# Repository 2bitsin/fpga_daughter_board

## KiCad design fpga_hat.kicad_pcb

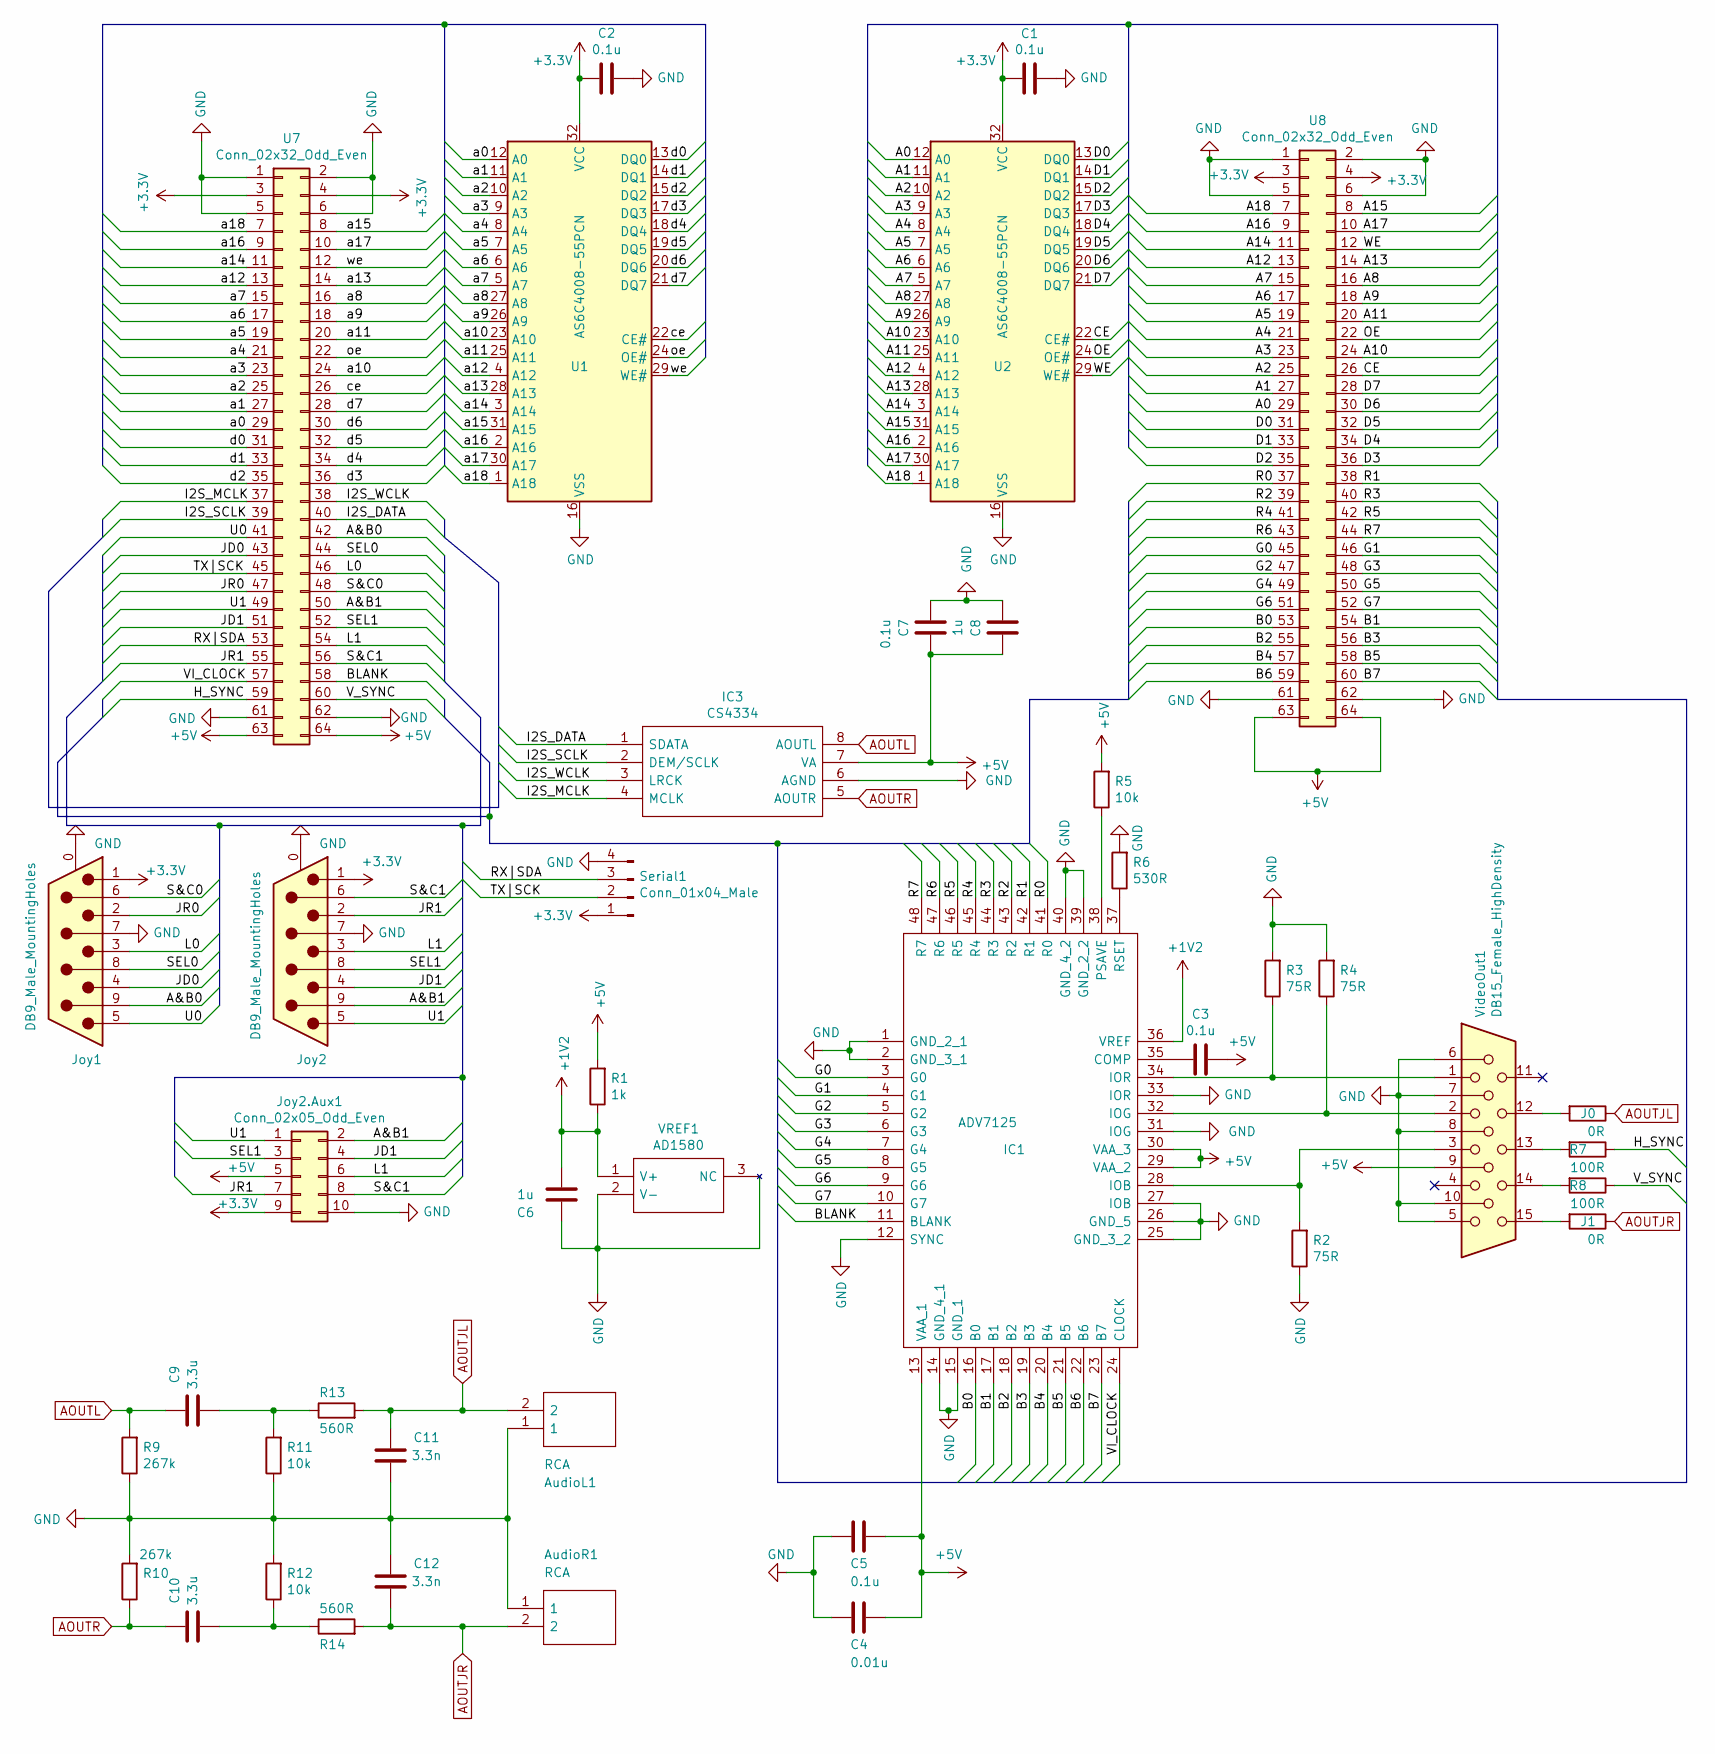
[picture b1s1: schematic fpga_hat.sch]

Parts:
AudioL1: RCA; KLPX0848A2RG
AudioR1: RCA; KLPX0848A2RG
C1, C2, C3, C5, C7: 0.1u; C_1206_3216Metric_Pad1.33x1.80mm_HandSolder
C4: 0.01u; C_1206_3216Metric_Pad1.33x1.80mm_HandSolder
C6, C8: 1u; C_1206_3216Metric_Pad1.33x1.80mm_HandSolder
C9, C10: 3.3u; C_1206_3216Metric_Pad1.33x1.80mm_HandSolder
C11, C12: 3.3n; C_1206_3216Metric_Pad1.33x1.80mm_HandSolder
IC1: ADV7125; QFP50P900X900X160-48N; Manufacturer_Part_Number ADV7125KSTZ50; Mouser Part Number 584-ADV7125KSTZ50
IC3: CS4334; SOIC127P600X175-8N; Mouser Part Number 777-CS4334-KSZ
J0, J1: 0R; R_0603_1608Metric
Joy1, Joy2: DB9_Male_MountingHoles; DSUB-9_Female_Horizontal_P2.77x2.84mm_EdgePinOffset4.94mm_H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
Joy2.Aux1: Conn_02x05_Odd_Even; PinHeader_2x05_P2.54mm_Vertical
R1: 1k; R_1206_3216Metric_Pad1.30x1.75mm_HandSolder
R2, R3, R4: 75R; R_1206_3216Metric_Pad1.30x1.75mm_HandSolder
R5, R11, R12: 10k; R_1206_3216Metric_Pad1.30x1.75mm_HandSolder
R6: 530R; R_1206_3216Metric_Pad1.30x1.75mm_HandSolder
R7, R8: 100R; R_1206_3216Metric_Pad1.30x1.75mm_HandSolder
R9, R10: 267k; R_1206_3216Metric_Pad1.30x1.75mm_HandSolder
R13, R14: 560R; R_1206_3216Metric_Pad1.30x1.75mm_HandSolder
Serial1: Conn_01x04_Male; PinHeader_1x04_P2.54mm_Vertical
U1, U2: AS6C4008-55PCN; DIP-32_W15.24mm
U7, U8: Conn_02x32_Odd_Even; PinHeader_2x32_P2.54mm_Vertical
VREF1: AD1580; SOT95P237X112-3N; Manufacturer_Part_Number AD1580BRTZ-REEL7; Mouser Part Number 584-AD1580BRTZ-R7
VideoOut1: DB15_Female_HighDensity; DSUB-15-HD_Female_Horizontal_P2.29x1.98mm_EdgePinOffset8.35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

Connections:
+1V2: C6.2, IC1.36 (VREF), R1.1, VREF1.1 (V+)
+3V3: C1.2, C2.2, Joy1.1, Joy2.1, Joy2.Aux1.9, Serial1.1, U1.32 (VCC), U2.32 (VCC), U7.3, U7.4, U8.3, U8.4
+5V: C3.1, C4.1, C5.1, C7.1, C8.1, IC1.13 (VAA_1), IC1.29 (VAA_2), IC1.30 (VAA_3), IC3.7 (VA), Joy2.Aux1.5, R1.2, R5.2, U7.63, U7.64, U8.63, U8.64, VideoOut1.9
/A0: U2.12 (A0), U8.29
/A1: U2.11 (A1), U8.27
/A2: U2.10 (A2), U8.25
/A3: U2.9 (A3), U8.23
/A4: U2.8 (A4), U8.21
/A5: U2.7 (A5), U8.19
/A6: U2.6 (A6), U8.17
/A7: U2.5 (A7), U8.15
/A8: U2.27 (A8), U8.16
/A9: U2.26 (A9), U8.18
/A10: U2.23 (A10), U8.24
/A11: U2.25 (A11), U8.20
/A12: U2.4 (A12), U8.13
/A13: U2.28 (A13), U8.14
/A14: U2.3 (A14), U8.11
/A15: U2.31 (A15), U8.8
/A16: U2.2 (A16), U8.9
/A17: U2.30 (A17), U8.10
/A18: U2.1 (A18), U8.7
/A&B0: Joy1.9, U7.42
/A&B1: Joy2.9, Joy2.Aux1.2, U7.50
/B0: IC1.16 (B0), U8.53
/B1: IC1.17 (B1), U8.54
/B2: IC1.18 (B2), U8.55
/B3: IC1.19 (B3), U8.56
/B4: IC1.20 (B4), U8.57
/B5: IC1.21 (B5), U8.58
/B6: IC1.22 (B6), U8.59
/B7: IC1.23 (B7), U8.60
/BLANK: IC1.11 (BLANK~), U7.58
/CE: U2.22 (CE#), U8.26
/D0: U2.13 (DQ0), U8.31
/D1: U2.14 (DQ1), U8.33
/D2: U2.15 (DQ2), U8.35
/D3: U2.17 (DQ3), U8.36
/D4: U2.18 (DQ4), U8.34
/D5: U2.19 (DQ5), U8.32
/D6: U2.20 (DQ6), U8.30
/D7: U2.21 (DQ7), U8.28
/G0: IC1.3 (G0), U8.45
/G1: IC1.4 (G1), U8.46
/G2: IC1.5 (G2), U8.47
/G3: IC1.6 (G3), U8.48
/G4: IC1.7 (G4), U8.49
/G5: IC1.8 (G5), U8.50
/G6: IC1.9 (G6), U8.51
/G7: IC1.10 (G7), U8.52
/H_SYNC: R7.1, U7.59
/I2S_DATA: IC3.1 (SDATA), U7.40
/I2S_MCLK: IC3.4 (MCLK), U7.37
/I2S_SCLK: IC3.2 (DEM/SCLK), U7.39
/I2S_WCLK: IC3.3 (LRCK), U7.38
/JD0: Joy1.4, U7.43
/JD1: Joy2.4, Joy2.Aux1.4, U7.51
/JR0: Joy1.2, U7.47
/JR1: Joy2.2, Joy2.Aux1.7, U7.55
/L0: Joy1.3, U7.46
/L1: Joy2.3, Joy2.Aux1.6, U7.54
/OE: U2.24 (OE#), U8.22
/R0: IC1.41 (R0), U8.37
/R1: IC1.42 (R1), U8.38
/R2: IC1.43 (R2), U8.39
/R3: IC1.44 (R3), U8.40
/R4: IC1.45 (R4), U8.41
/R5: IC1.46 (R5), U8.42
/R6: IC1.47 (R6), U8.43
/R7: IC1.48 (R7), U8.44
/RX|SDA: Serial1.3, U7.53
/S&C0: Joy1.6, U7.48
/S&C1: Joy2.6, Joy2.Aux1.8, U7.56
/SEL0: Joy1.8, U7.44
/SEL1: Joy2.8, Joy2.Aux1.3, U7.52
/TX|SCK: Serial1.2, U7.45
/U0: Joy1.5, U7.41
/U1: Joy2.5, Joy2.Aux1.1, U7.49
/VI_CLOCK: IC1.24 (CLOCK), U7.57
/V_SYNC: R8.1, U7.60
/WE: U2.29 (WE#), U8.12
/a0: U1.12 (A0), U7.29
/a1: U1.11 (A1), U7.27
/a2: U1.10 (A2), U7.25
/a3: U1.9 (A3), U7.23
/a4: U1.8 (A4), U7.21
/a5: U1.7 (A5), U7.19
/a6: U1.6 (A6), U7.17
/a7: U1.5 (A7), U7.15
/a8: U1.27 (A8), U7.16
/a9: U1.26 (A9), U7.18
/a10: U1.23 (A10), U7.24
/a11: U1.25 (A11), U7.20
/a12: U1.4 (A12), U7.13
/a13: U1.28 (A13), U7.14
/a14: U1.3 (A14), U7.11
/a15: U1.31 (A15), U7.8
/a16: U1.2 (A16), U7.9
/a17: U1.30 (A17), U7.10
/a18: U1.1 (A18), U7.7
/ce: U1.22 (CE#), U7.26
/d0: U1.13 (DQ0), U7.31
/d1: U1.14 (DQ1), U7.33
/d2: U1.15 (DQ2), U7.35
/d3: U1.17 (DQ3), U7.36
/d4: U1.18 (DQ4), U7.34
/d5: U1.19 (DQ5), U7.32
/d6: U1.20 (DQ6), U7.30
/d7: U1.21 (DQ7), U7.28
/oe: U1.24 (OE#), U7.22
/we: U1.29 (WE#), U7.12
AOUTJL: AudioL1.2, C11.1, J0.1, R13.2
AOUTJR: AudioR1.2, C12.2, J1.1, R14.2
AOUTL: C9.1, IC3.8 (AOUTL), R9.2
AOUTR: C10.1, IC3.5 (AOUTR), R10.1
GND: AudioL1.1, AudioR1.1, C1.1, C2.1, C4.2, C5.2, C6.1, C7.2, C8.2, C11.2, C12.1, IC1.1 (GND_2_1), IC1.2 (GND_3_1), IC1.12 (SYNC~), IC1.14 (GND_4_1), IC1.15 (GND_1), IC1.25 (GND_3_2), IC1.26 (GND_5), IC1.27 (IOB~), IC1.31 (IOG~), IC1.33 (IOR~), IC1.39 (GND_2_2), IC1.40 (GND_4_2), IC3.6 (AGND), Joy1.0 (PAD), Joy1.7, Joy2.0 (PAD), Joy2.7, Joy2.Aux1.10, R2.1, R3.2, R4.2, R6.2, R9.1, R10.2, R11.1, R12.2, Serial1.4, U1.16 (VSS), U2.16 (VSS), U7.1, U7.2, U7.5, U7.6, U7.61, U7.62, U8.1, U8.2, U8.5, U8.6, U8.61, U8.62, VREF1.2 (V-), VREF1.3 (NC), VideoOut1.5, VideoOut1.6, VideoOut1.7, VideoOut1.8, VideoOut1.10
unnamed: C3.2, IC1.35 (COMP)
unnamed: C9.2, R11.2, R13.1
unnamed: C10.2, R12.1, R14.1
unnamed: IC1.28 (IOB), R2.2, VideoOut1.3
unnamed: IC1.32 (IOG), R4.1, VideoOut1.2
unnamed: IC1.34 (IOR), R3.1, VideoOut1.1
unnamed: IC1.37 (RSET), R6.1
unnamed: IC1.38 (PSAVE~), R5.1
unnamed: J0.2, VideoOut1.12
unnamed: J1.2, VideoOut1.15
unnamed: R7.2, VideoOut1.13
unnamed: R8.2, VideoOut1.14

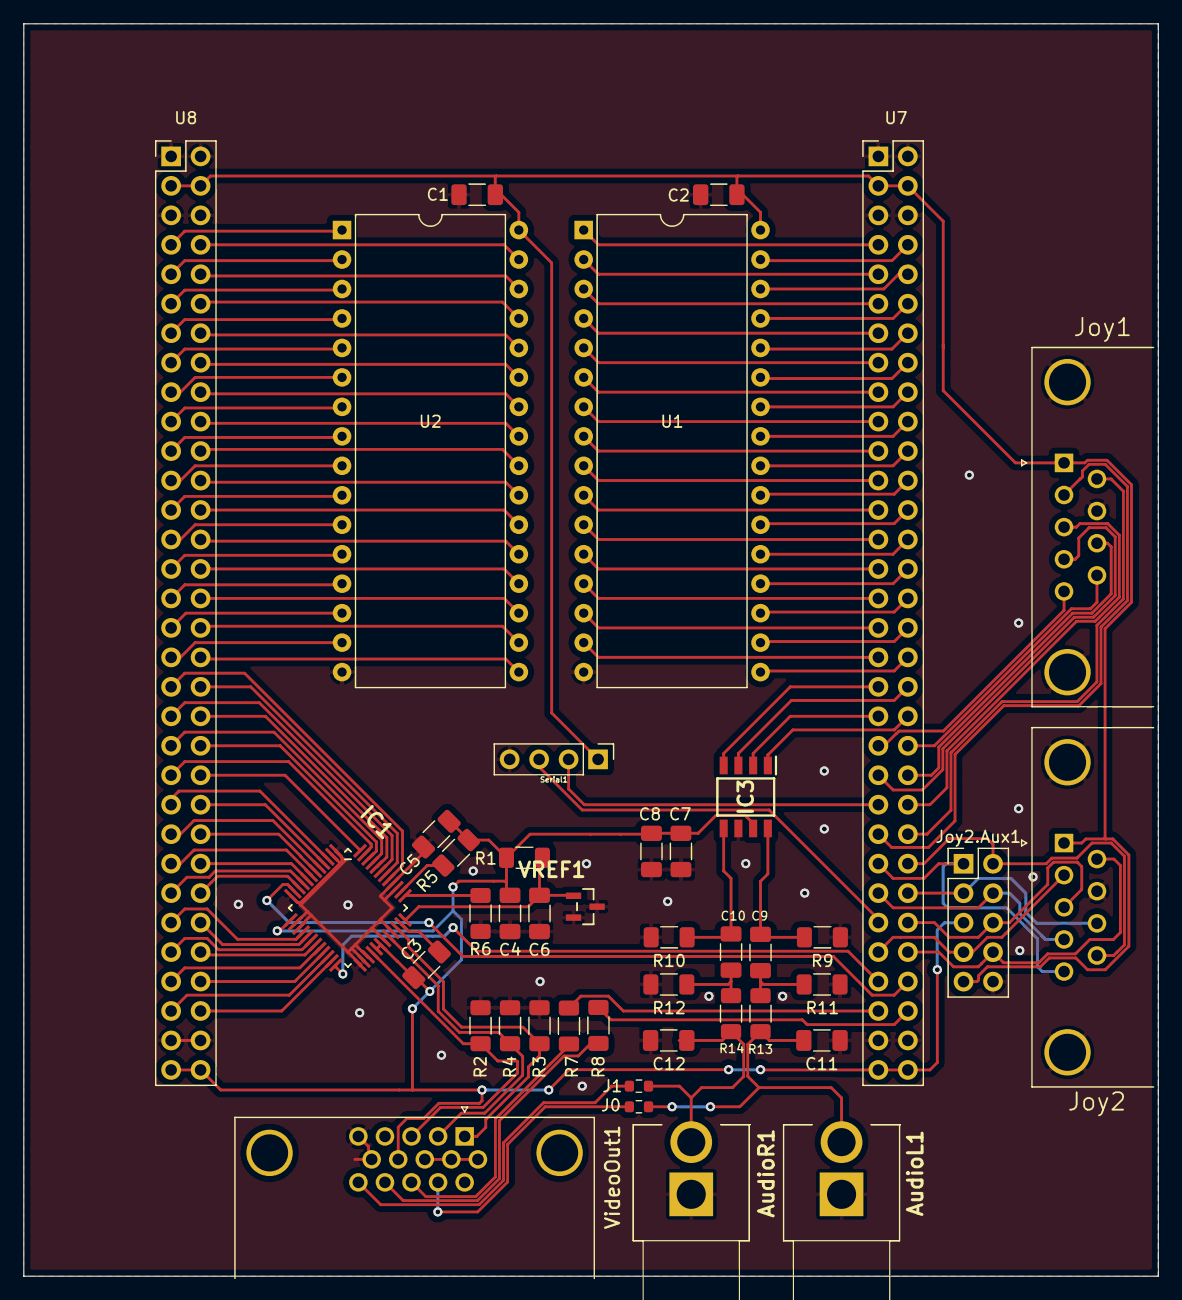
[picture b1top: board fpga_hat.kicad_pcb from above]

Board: 2 copper layers, 97.8 x 108.0 mm, 42 parts (0 on the bottom side), 128 nets.

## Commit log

2020-12-04 Initial
2021-04-02 Fixed bad audio routing, added jumper points for running audio trough the vga jack, added missing footprints/symbols
2021-06-10 Fixed gamepad port routing
